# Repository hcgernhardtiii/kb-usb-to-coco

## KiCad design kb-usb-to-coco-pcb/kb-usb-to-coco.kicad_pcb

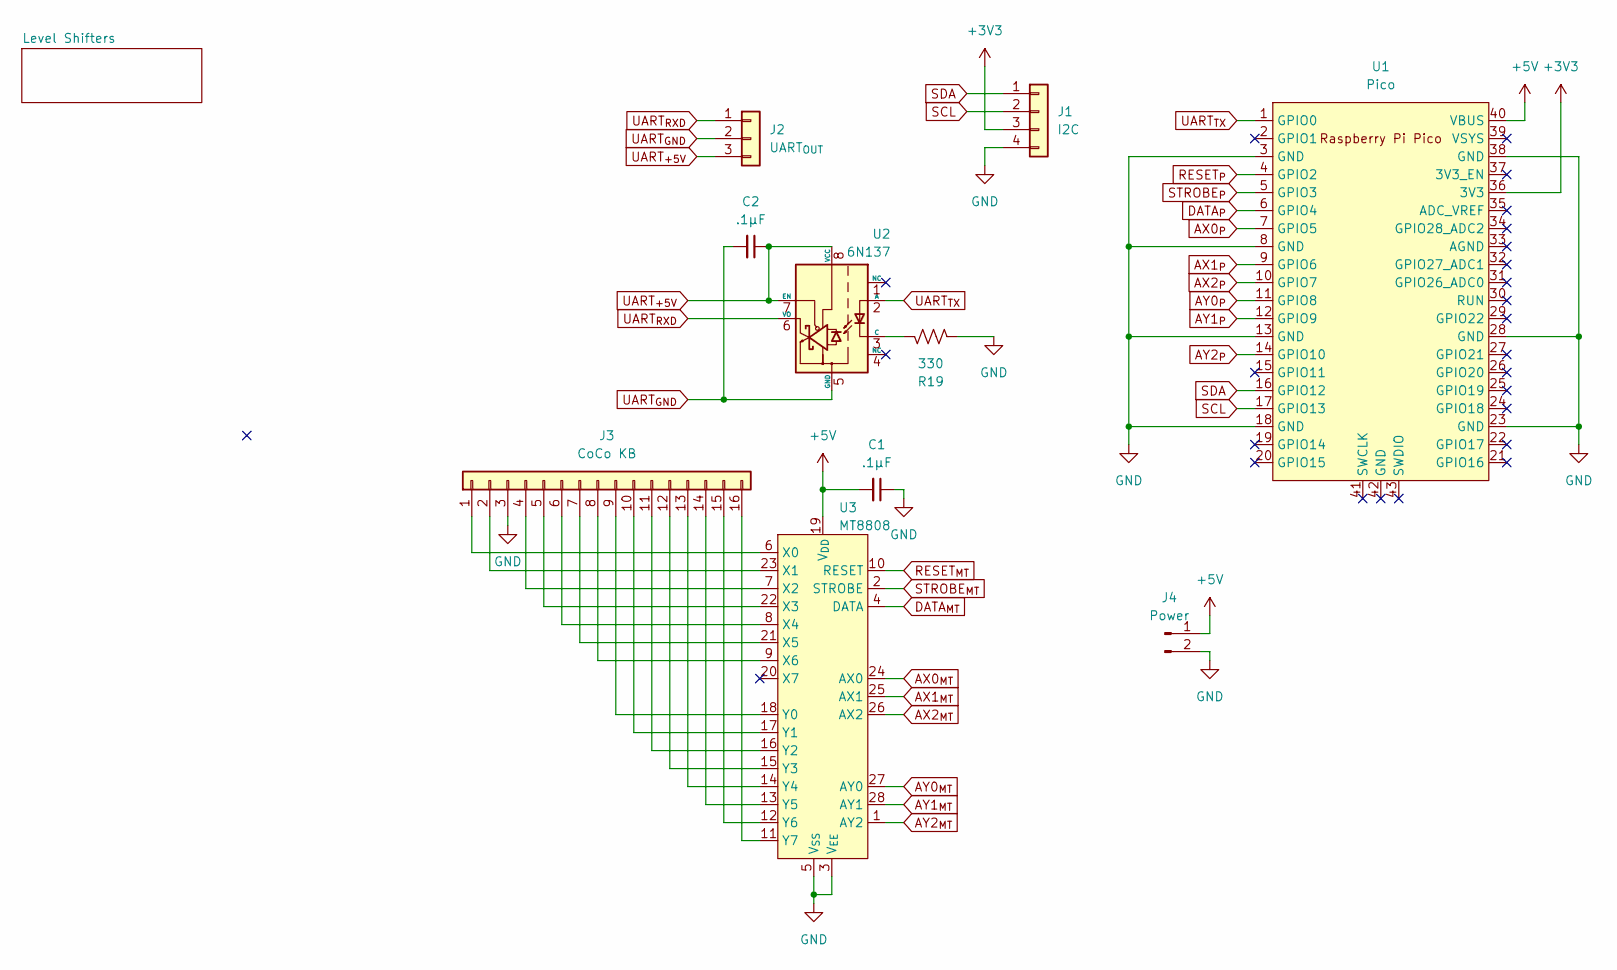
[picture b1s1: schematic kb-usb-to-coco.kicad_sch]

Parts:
C1, C2: .1µF; C_Disc_D6.0mm_W2.5mm_P5.00mm
J1: I2C; PinHeader_1x04_P2.54mm_Vertical
J2: UART_{OUT}; PinHeader_1x03_P2.54mm_Vertical
J3: CoCo KB; PinHeader_1x16_P2.54mm_Vertical
J4: Power; PinHeader_1x02_P2.54mm_Vertical
R19: 330; R_Axial_DIN0207_L6.3mm_D2.5mm_P7.62mm_Horizontal
U1: Pico; RPi_Pico_SMD_TH
U2: 6N137; DIP-8_W7.62mm_Socket_LongPads
U3: MT8808; DIP-28_W15.24mm_Socket_LongPads

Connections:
+3V3: J1.3, U1.36 (3V3); also elsewhere on the board
+5V: C1.2, J4.1, U1.40 (VBUS), U3.19 (V_{DD}); also elsewhere on the board
AX0_{MT}: U3.24 (AX0); also elsewhere on the board
AX0_{P}: U1.7 (GPIO5); also elsewhere on the board
AX1_{MT}: U3.25 (AX1); also elsewhere on the board
AX1_{P}: U1.9 (GPIO6); also elsewhere on the board
AX2_{MT}: U3.26 (AX2); also elsewhere on the board
AX2_{P}: U1.10 (GPIO7); also elsewhere on the board
AY0_{MT}: U3.27 (AY0); also elsewhere on the board
AY0_{P}: U1.11 (GPIO8); also elsewhere on the board
AY1_{MT}: U3.28 (AY1); also elsewhere on the board
AY1_{P}: U1.12 (GPIO9); also elsewhere on the board
AY2_{MT}: U3.1 (AY2); also elsewhere on the board
AY2_{P}: U1.14 (GPIO10); also elsewhere on the board
DATA_{MT}: U3.4 (DATA); also elsewhere on the board
DATA_{P}: U1.6 (GPIO4); also elsewhere on the board
GND: C1.1, J1.4, J3.3, J4.2, R19.1, U1.3 (GND), U1.8 (GND), U1.13 (GND), U1.18 (GND), U1.23 (GND), U1.28 (GND), U1.38 (GND), U3.3 (V_{EE}), U3.5 (V_{SS})
unnamed: J3.1, U3.6 (X0)
unnamed: J3.2, U3.23 (X1)
unnamed: J3.4, U3.7 (X2)
unnamed: J3.5, U3.22 (X3)
unnamed: J3.6, U3.8 (X4)
unnamed: J3.7, U3.21 (X5)
unnamed: J3.8, U3.9 (X6)
unnamed: J3.9, U3.18 (Y0)
unnamed: J3.10, U3.17 (Y1)
unnamed: J3.11, U3.16 (Y2)
unnamed: J3.12, U3.15 (Y3)
unnamed: J3.13, U3.14 (Y4)
unnamed: J3.14, U3.13 (Y5)
unnamed: J3.15, U3.12 (Y6)
unnamed: J3.16, U3.11 (Y7)
unnamed: R19.2, U2.3 (C)
RESET_{MT}: U3.10 (RESET); also elsewhere on the board
RESET_{P}: U1.4 (GPIO2); also elsewhere on the board
SCL: J1.2, U1.17 (GPIO13)
SDA: J1.1, U1.16 (GPIO12)
STROBE_{MT}: U3.2 (STROBE); also elsewhere on the board
STROBE_{P}: U1.5 (GPIO3); also elsewhere on the board
UART_{+5V}: C2.1, J2.3, U2.7 (EN), U2.8 (VCC)
UART_{GND}: C2.2, J2.2, U2.5 (GND)
UART_{RXD}: J2.1, U2.6 (VO)
UART_{TX}: U1.1 (GPIO0), U2.2 (A)

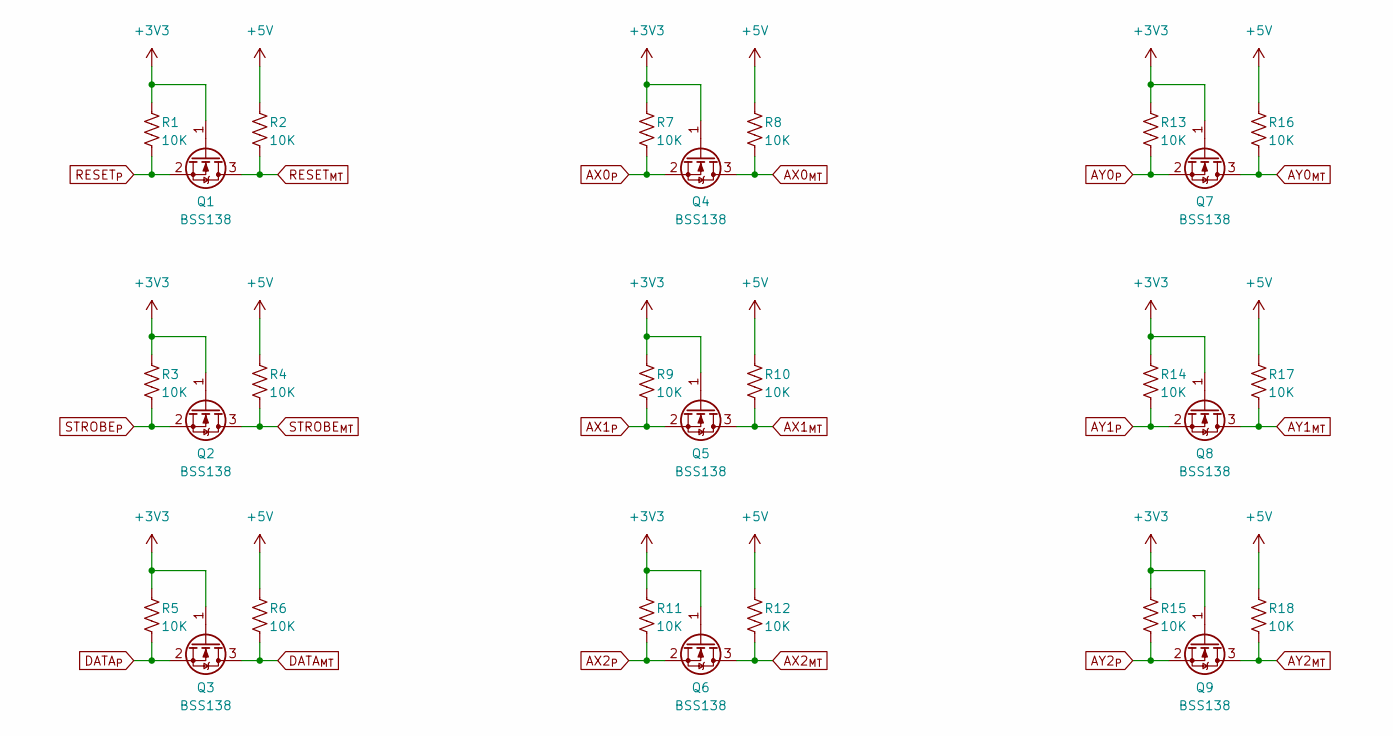
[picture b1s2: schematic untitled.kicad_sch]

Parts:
Q1, Q2, Q3, Q4, Q5, Q6, Q7, Q8, Q9: BSS138; SOT-23
R1, R2, R3, R4, R5, R6, R7, R8, R9, R10, R11, R12, R13, R14, R15, R16, R17, R18: 10K; R_0603_1608Metric

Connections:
+3V3: Q1.1 (G), Q2.1 (G), Q3.1 (G), Q4.1 (G), Q5.1 (G), Q6.1 (G), Q7.1 (G), Q8.1 (G), Q9.1 (G), R1.1, R3.1, R5.1, R7.1, R9.1, R11.1, R13.1, R14.1, R15.1; also elsewhere on the board
+5V: R2.1, R4.1, R6.1, R8.1, R10.1, R12.1, R16.1, R17.1, R18.1; also elsewhere on the board
AX0_{MT}: Q4.3 (D), R8.2; also elsewhere on the board
AX0_{P}: Q4.2 (S), R7.2; also elsewhere on the board
AX1_{MT}: Q5.3 (D), R10.2; also elsewhere on the board
AX1_{P}: Q5.2 (S), R9.2; also elsewhere on the board
AX2_{MT}: Q6.3 (D), R12.2; also elsewhere on the board
AX2_{P}: Q6.2 (S), R11.2; also elsewhere on the board
AY0_{MT}: Q7.3 (D), R16.2; also elsewhere on the board
AY0_{P}: Q7.2 (S), R13.2; also elsewhere on the board
AY1_{MT}: Q8.3 (D), R17.2; also elsewhere on the board
AY1_{P}: Q8.2 (S), R14.2; also elsewhere on the board
AY2_{MT}: Q9.3 (D), R18.2; also elsewhere on the board
AY2_{P}: Q9.2 (S), R15.2; also elsewhere on the board
DATA_{MT}: Q3.3 (D), R6.2; also elsewhere on the board
DATA_{P}: Q3.2 (S), R5.2; also elsewhere on the board
RESET_{MT}: Q1.3 (D), R2.2; also elsewhere on the board
RESET_{P}: Q1.2 (S), R1.2; also elsewhere on the board
STROBE_{MT}: Q2.3 (D), R4.2; also elsewhere on the board
STROBE_{P}: Q2.2 (S), R3.2; also elsewhere on the board

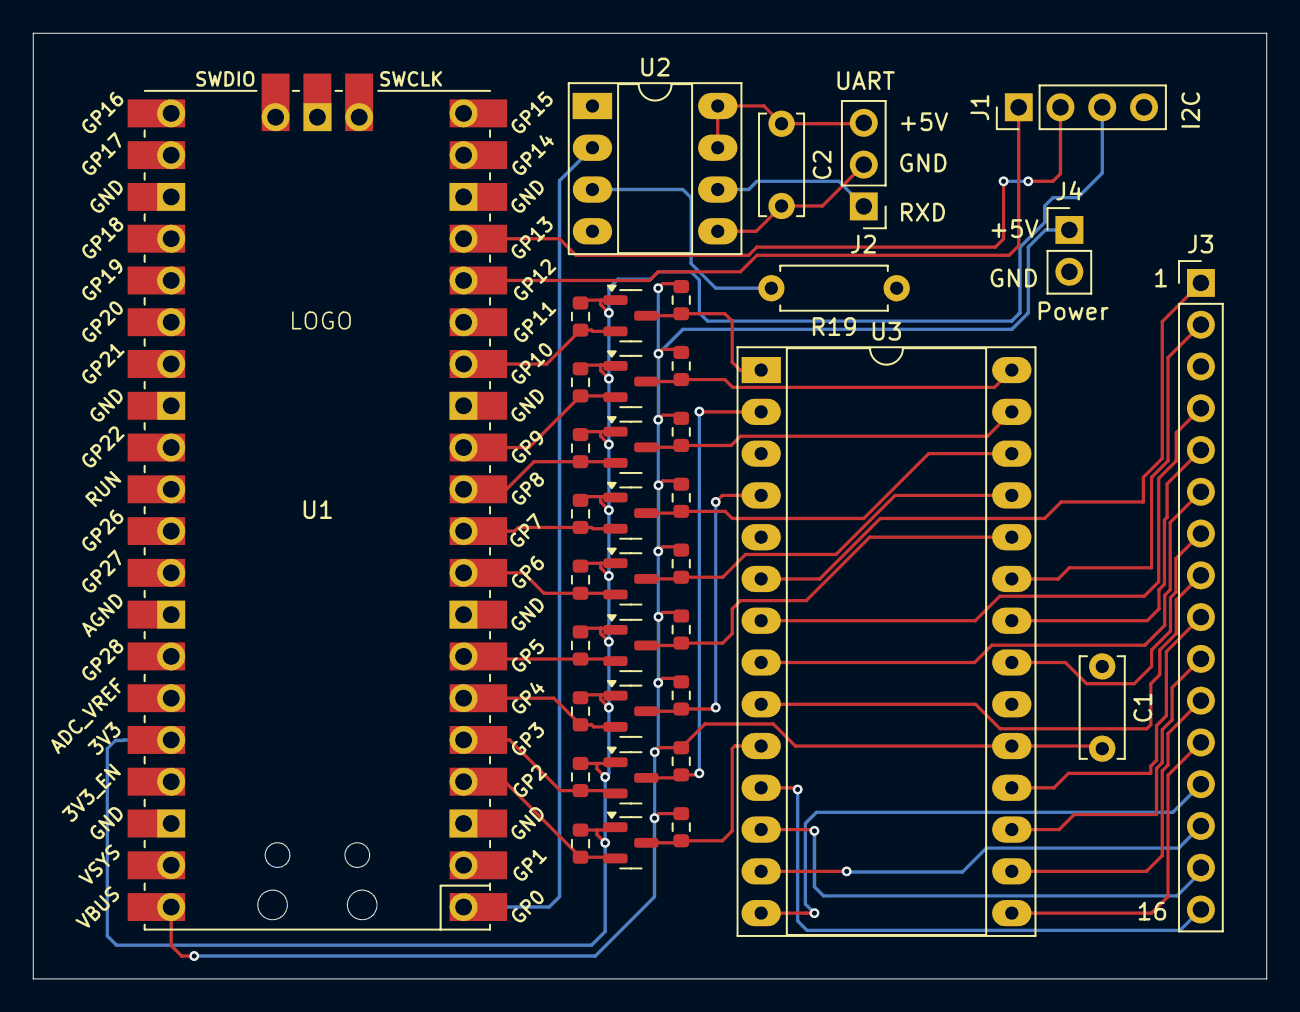
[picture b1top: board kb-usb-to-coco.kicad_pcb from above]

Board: 2 copper layers, 75.0 x 57.5 mm, 38 parts (0 on the bottom side), 43 nets.

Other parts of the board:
LOGO: tbk-logo

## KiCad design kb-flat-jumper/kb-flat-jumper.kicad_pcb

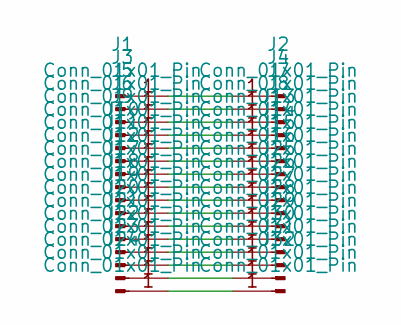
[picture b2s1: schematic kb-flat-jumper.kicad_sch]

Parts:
J1, J2, J3, J4, J5, J6, J7, J8, J9, J10, J11, J12, J13, J14, J15, J16, J17, J18, J19, J20, J21, J22, J23, J24, J25, J26, J27, J28, J29, J30, J31, J32: Conn_01x01_Pin; pad_1.27mm_5.588mm

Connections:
unnamed: J1.1, J2.1
unnamed: J3.1, J4.1
unnamed: J5.1, J7.1
unnamed: J6.1, J8.1
unnamed: J10.1, J14.1
unnamed: J11.1, J15.1
unnamed: J12.1, J16.1
unnamed: J9.1, J13.1
unnamed: J17.1, J25.1
unnamed: J18.1, J26.1
unnamed: J19.1, J27.1
unnamed: J20.1, J28.1
unnamed: J21.1, J29.1
unnamed: J22.1, J30.1
unnamed: J23.1, J31.1
unnamed: J24.1, J32.1

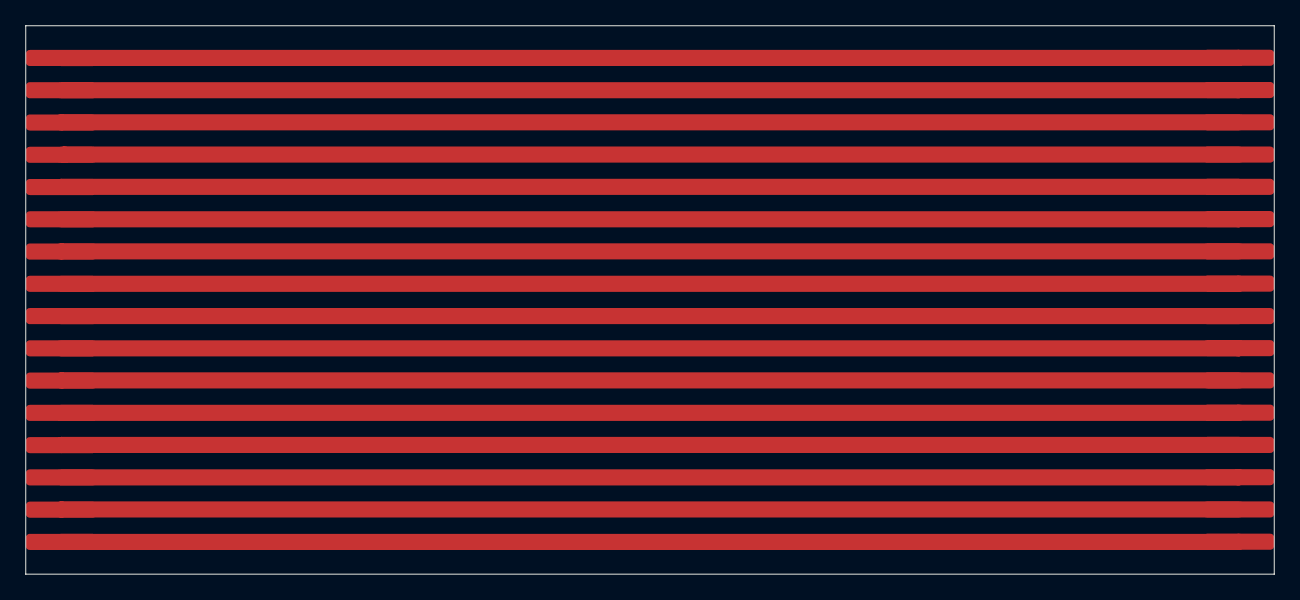
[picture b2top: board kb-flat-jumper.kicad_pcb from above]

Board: 2 copper layers, 98.3 x 43.2 mm, 32 parts (0 on the bottom side), 16 nets.

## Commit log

2025-03-23 Hardware for CoCo only is complete Firmware is currently set up for direct only
2025-03-23 Added all the things I talked about in the last commit message
2025-03-23 Added branch for video creation. Commit made after each stage.
2025-03-25 Episode 4: commit 1: basic refactoring
2025-03-25 Episode 4: Commit 2: State variables and their explanations
2025-03-26 Episode 4: Commit 3: Matrixify the HID report
2025-03-28 Episode 4: Commit 4: Refactoring the raw mode
2025-03-28 Episode 4: Commit 5: Make sure the mode switch works (<kbd>GUI</kbd>+<kbd>Z</kbd>
2025-03-28 Episode 4: Commit 6: Oops, we've hit a snag of simultinaity!
2025-03-28 Episode 4: Commit 7: Looks like we've resolved the key conflict issue for now
2025-03-28 Episode 4: Commit 8: We'll be taking a break for a bit before resolving any further keypress conflicts
2025-03-29 Episode 4: Take Two: Commit 6: Rethinking the mapped mode
2025-03-29 Episode 4: Take two: Commit 7: Breaking out some QOL functions
2025-03-29 Episode 4: Take two: Commit 8: Getting keycodes back is working.
2025-03-29 Episode 4: Take 2: Commit 9: It *mostly* works. Maybe timing?
2025-03-29 Episode 4: Take two: Commit 10: It's working well!
2025-03-30 Added mapped mode
2025-03-31 Episode 4: Everything is working now. I'll merge this back into HEAD.
2025-04-02 Episode 4: We Have Mapped Mode!
2025-04-22 Starting Episode 5: Resolving Diffs
2025-04-27 Episode 5: Adding an OLED Indication Screen
